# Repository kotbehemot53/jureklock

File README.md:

# jureklock
A simple IR-controlled electronic door lock with a little game.

## Main board schematic

## Interface board schematic

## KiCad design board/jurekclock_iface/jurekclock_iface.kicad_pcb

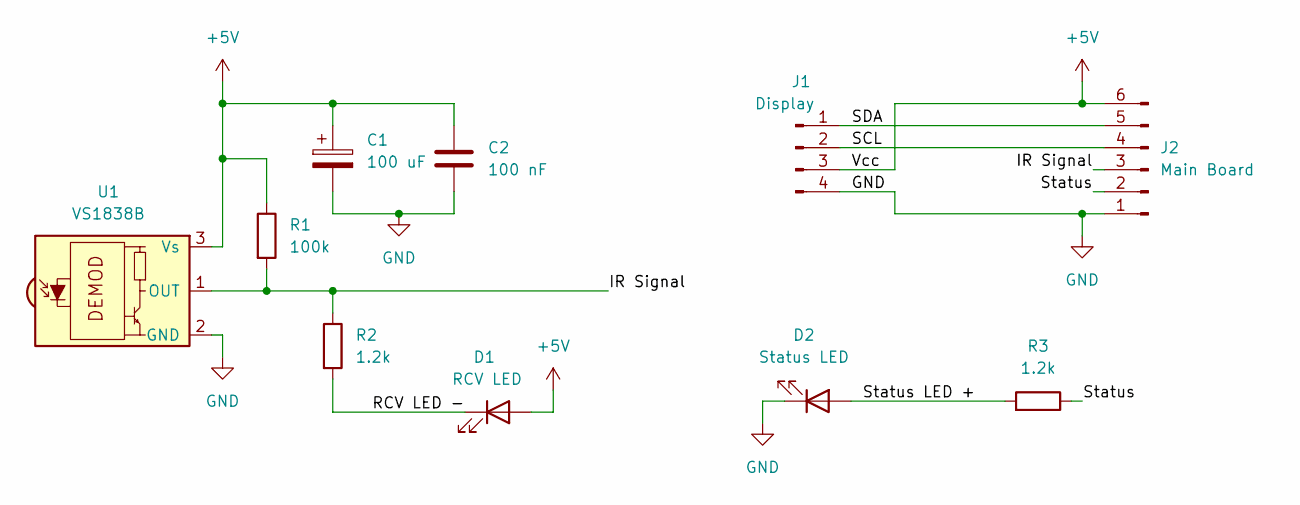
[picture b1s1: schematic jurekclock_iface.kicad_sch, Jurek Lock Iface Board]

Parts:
C1: 100 uF; CP_Radial_D6.3mm_P2.50mm
C2: 100 nF; C_Disc_D5.0mm_W2.5mm_P2.50mm
D1: RCV LED; LED_D3.0mm
D2: Status LED; LED_D3.0mm
J1: Display; PinHeader_1x04_P2.54mm_Vertical
J2: Main Board; JST_XH_B6B-XH-A_1x06_P2.50mm_Vertical
R1: 100k; R_Axial_DIN0207_L6.3mm_D2.5mm_P7.62mm_Horizontal
R2, R3: 1.2k; R_Axial_DIN0207_L6.3mm_D2.5mm_P7.62mm_Horizontal
U1: VS1838B; Vishay_MOLD-3Pin

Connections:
+5V: C1.1, C2.1, D1.2 (A), J1.3, J2.6, R1.1, U1.3 (Vs)
/IR Signal: J2.3, R1.2, R2.1, U1.1 (OUT)
/RCV LED -: D1.1 (K), R2.2
/SCL: J1.2, J2.4
/SDA: J1.1, J2.5
/Status: J2.2, R3.1
/Status LED +: D2.2 (A), R3.2
GND: C1.2, C2.2, D2.1 (K), J1.4, J2.1, U1.2 (GND)

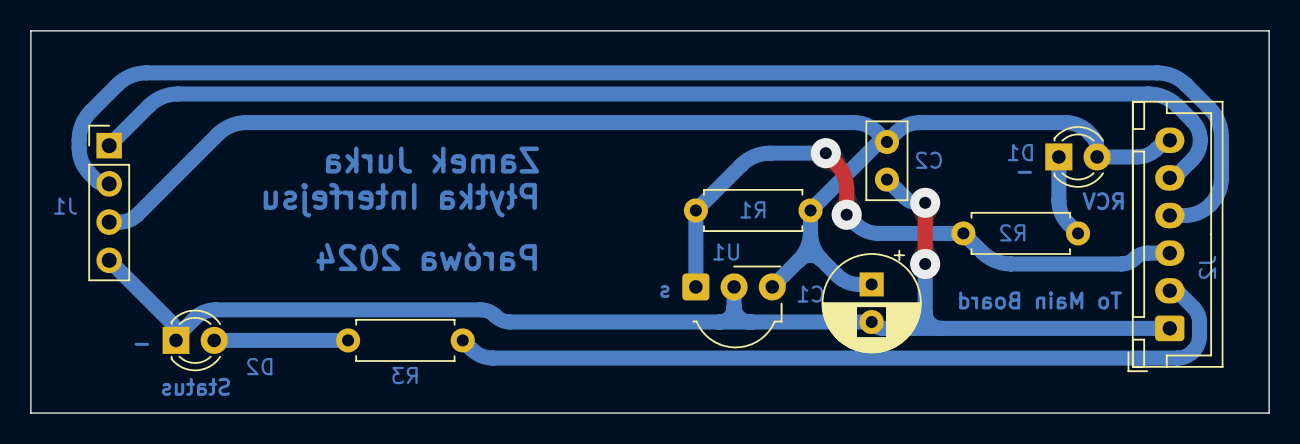
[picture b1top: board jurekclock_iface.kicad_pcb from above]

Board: 2 copper layers, 82.3 x 25.4 mm, 10 parts (0 on the bottom side), 8 nets.

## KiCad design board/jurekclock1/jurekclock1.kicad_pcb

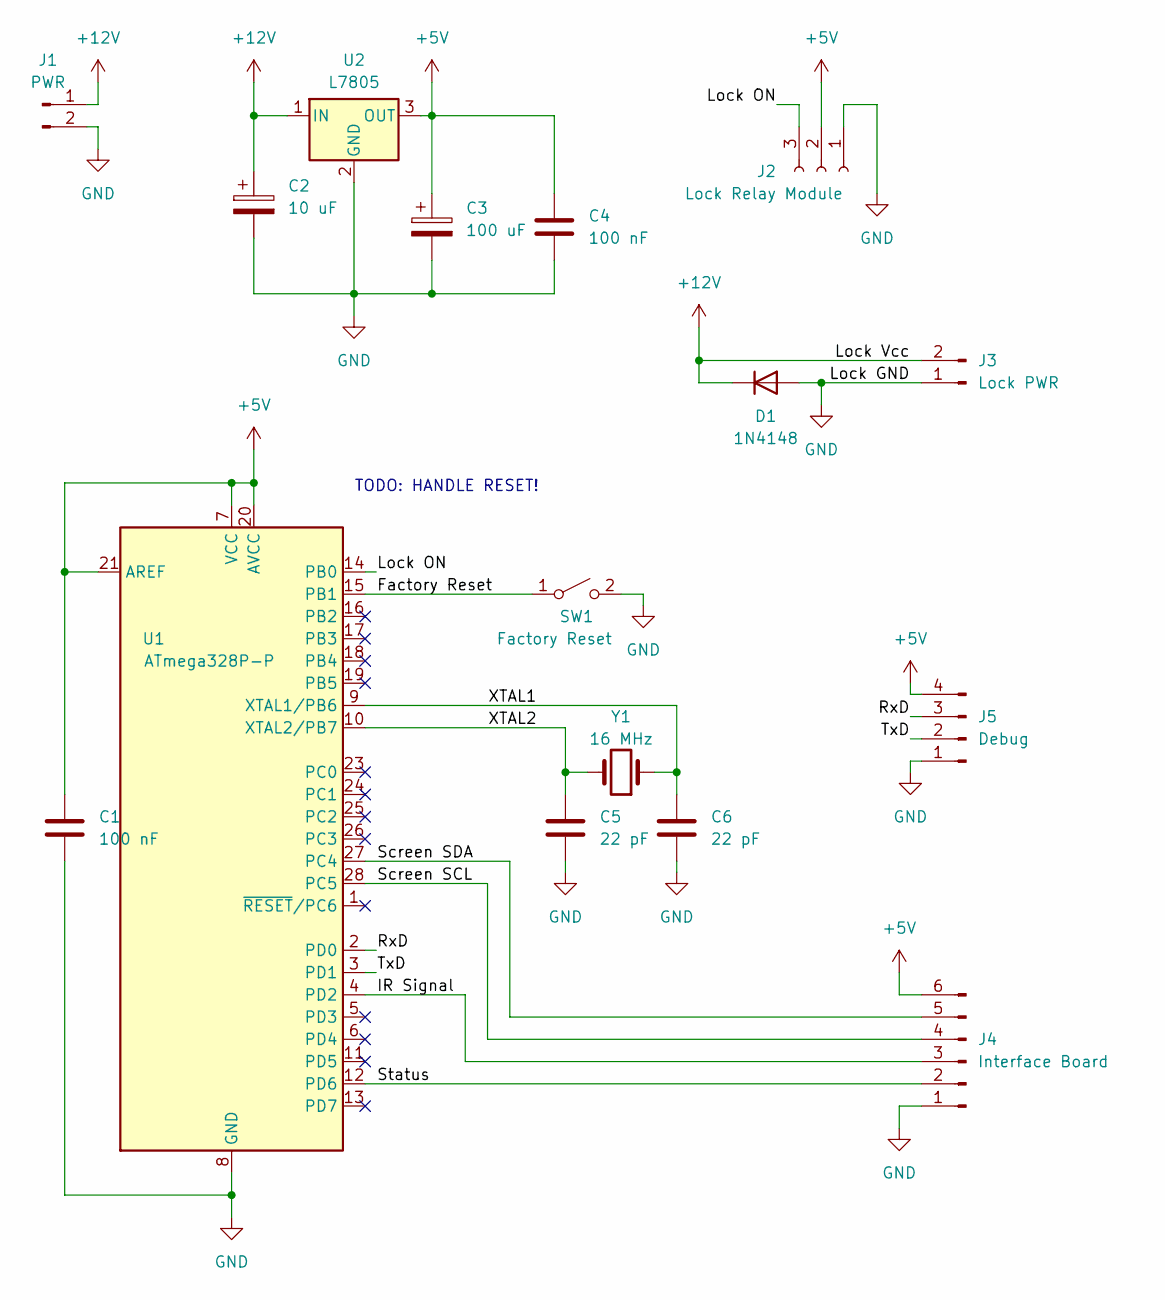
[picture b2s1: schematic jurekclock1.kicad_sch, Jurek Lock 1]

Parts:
C1, C4: 100 nF; C_Disc_D5.0mm_W2.5mm_P2.50mm
C2: 10 uF; CP_Radial_D6.3mm_P2.50mm
C3: 100 uF; CP_Radial_D6.3mm_P2.50mm
C5, C6: 22 pF; C_Disc_D3.0mm_W2.0mm_P2.50mm
D1: 1N4148; D_DO-35_SOD27_P7.62mm_Horizontal
J1: PWR; JST_XH_B2B-XH-A_1x02_P2.50mm_Vertical
J2: Lock Relay Module; PinSocket_1x03_P2.54mm_Vertical
J3: Lock PWR; JST_XH_B2B-XH-A_1x02_P2.50mm_Vertical
J4: Interface Board; JST_XH_B6B-XH-A_1x06_P2.50mm_Vertical
J5: Debug; PinHeader_1x04_P2.54mm_Vertical
SW1: Factory Reset; SW_PUSH_6mm_H5mm
U1: ATmega328P-P; DIP-28_W7.62mm_Socket
U2: L7805; TO-220-3_Vertical
Y1: 16 MHz; Crystal_HC49-4H_Vertical

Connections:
+5V: C1.1, C3.1, C4.1, J2.2, J4.6, J5.4, U1.7 (VCC), U1.20 (AVCC), U1.21 (AREF), U2.3 (OUT)
+12V: C2.1, D1.1 (K), J1.1, J3.2, U2.1 (IN)
/Factory Reset: SW1.1 (A), U1.15 (PB1)
/IR Signal: J4.3, U1.4 (PD2)
/Lock ON: J2.3, U1.14 (PB0)
/RxD: J5.3, U1.2 (PD0)
/Screen SCL: J4.4, U1.28 (PC5)
/Screen SDA: J4.5, U1.27 (PC4)
/Status: J4.2, U1.12 (PD6)
/TxD: J5.2, U1.3 (PD1)
/XTAL1: C6.1, U1.9 (XTAL1/PB6), Y1.1
/XTAL2: C5.1, U1.10 (XTAL2/PB7), Y1.2
GND: C1.2, C2.2, C3.2, C4.2, C5.2, C6.2, D1.2 (A), J1.2, J2.1, J3.1, J4.1, J5.1, SW1.2 (B), U1.8 (GND), U1.22 (GND), U2.2 (GND)

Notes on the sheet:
TODO: HANDLE RESET!

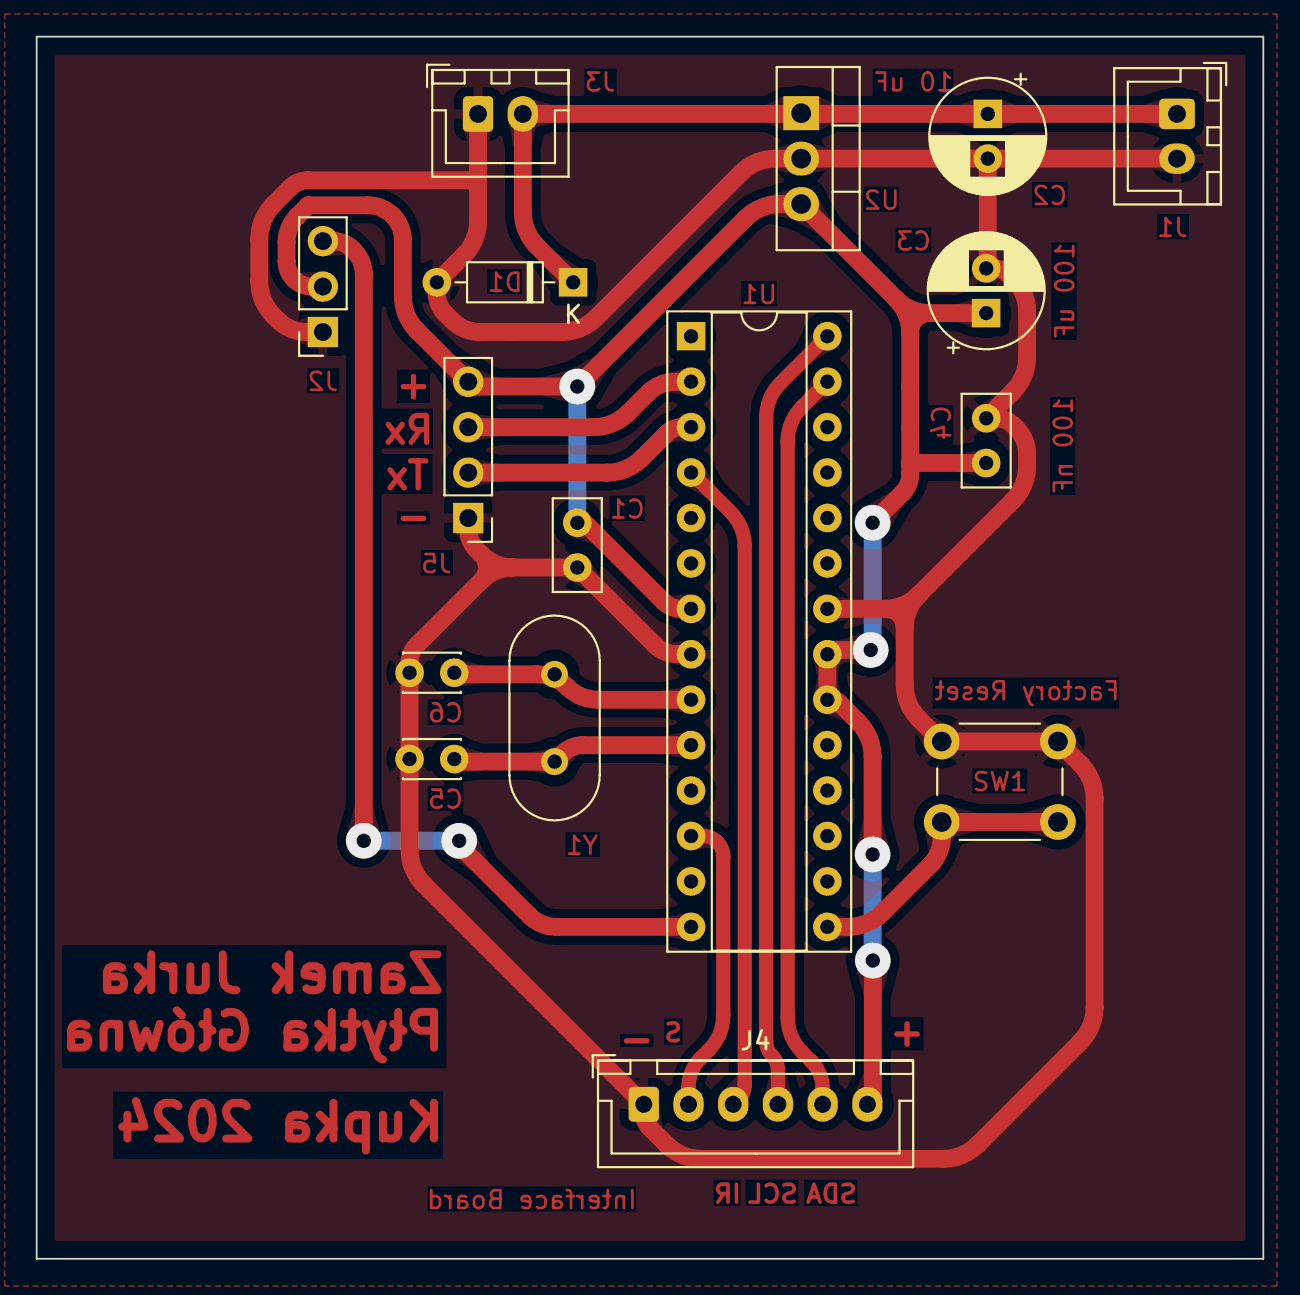
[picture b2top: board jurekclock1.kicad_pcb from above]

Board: 2 copper layers, 68.6 x 68.3 mm, 16 parts (0 on the bottom side), 13 nets.

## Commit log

2023-12-26 moar init
2023-12-26 cleanup
2023-12-27 reading code input
2023-12-27 some constants
2023-12-27 checking code, opening door, setting code when door open
2023-12-27 factory reset, status pin
2023-12-27 proper button support, status led blinking
2023-12-27 cleanup, schedule locking with timer
2023-12-27 random todos
2023-12-27 some todos, button names display
2023-12-29 added build config for external atmega using internal oscillator
2023-12-29 failed attempt at UPLOAD UART...
2024-01-07 config update
2024-01-07 boards
2024-01-10 board changes
2024-01-10 u8g2 test 1
2024-01-11 screen test 2
2024-01-12 full buffer screen approach
2024-01-13 paged appr again
2024-01-13 screen clearing added
2024-01-13 init version of da goym
2024-01-13 gradual speedup of the game
2024-01-15 RAM optimization
2024-01-16 no moar warningz
2024-01-16 watchdog introduced at 2s
2024-01-16 game drawing and screen clearing cleanup
2024-01-16 ir parity check
2024-01-16 game cleanup
2024-01-16 unnecessary screen clear removed
2024-01-17 just a todo
2024-01-17 vscode gitignore
2024-01-17 wokwi
2024-01-17 drawing score live
2024-01-17 2-page rendering + score rounding fix WIP - the thing seems SLOW - use full frame?
2024-01-17 full buffer for screen
2024-01-17 comment cleanup
2024-01-17 correct score counting
2024-01-17 obstacle negative positions
2024-01-17 minor Lock refac
2024-01-17 wokwi environment
2024-01-17 platformio.ini cleanup
2024-01-17 readme & gitignore update
2024-01-17 old bkp dir removed
2024-01-17 schematic images
2024-01-17 game over text change
2024-01-17 define -> const
2024-01-20 some todos and comments
2024-01-20 CodeManager class
2024-01-21 lil reorg
2024-01-21 CodeManager dir
2024-01-21 lock class added
2024-01-21 CodeBuffer & RemoteInput
2024-01-23 TaskScheduler WIP - TODO replace all uses of timer!
2024-01-25 TaskScheduler working
2024-01-28 proper oop with OO Scheduler WIP
2024-01-28 LockScheduler
2024-01-28 ScreenOutput
2024-01-30 game over screen refac
2024-01-30 state manager & reset scheduler
2024-01-30 a bit of a cleanup
2024-01-30 moar cleanup
2024-01-31 cosmetic changes
